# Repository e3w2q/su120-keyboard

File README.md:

# 

Expandable keyboard PCB with up to 120 keys.

## What is the SU120?

The SU120 is an assemblable and expandable keyboard PCB with biscuits, screws and wire.

I use JIS Kana input method, but at that time I couldn't find  split JIS keyboard PCBs.

So I designed the PCB to make the keyboard layout easy to trial and error.

You may make Row-Staggered, Column-Staggerd, Ortholinear, or other layouts keyboard.

SU is Japanese homophones: 州(sandbank) and 鬆(porous).

## Why open source?

Anyone interested in keyboard could try the keyboard layout more easily.

## Link

[Hardware data (PCB)](/pcb/)

[Plate data (PCB)](/plate-pcb/)

[PCB Order Guide](https://github.com/e3w2q/su120-keyboard-doc/blob/master/common/pcb_order_guide.md) / [PCBの入手方法](https://github.com/e3w2q/su120-keyboard-doc/blob/master/common/pcb_order_guide_jp.md)

[Firmware](https://github.com/e3w2q/qmk_firmware/tree/e3w2q/keyboards/e3w2q/su120)

[Remap/VIA Firmware Hex File](/firmware/)

[How to create a custom layout](https://github.com/e3w2q/su120-keyboard-doc/blob/master/custom-layout/readme.md) / [自由なレイアウトを作成するには](https://github.com/e3w2q/su120-keyboard-doc/blob/master/custom-layout/readme_jp.md)

## Example

### 15 Key (+2 Knob) Keypad

[ビルドガイド](https://github.com/e3w2q/su120-keyboard-doc/blob/master/sasami17/readme_jp.md)

### 30 Key Ortholinear Keyboard

[ビルドガイド](https://github.com/e3w2q/su120-keyboard-doc/blob/master/sasami30/readme_jp.md)

### 120 Key Split Ortholinear Keyboard 

[ビルドガイド](https://github.com/e3w2q/su120-keyboard-doc/blob/master/momo120/readme_jp.md)

### 40% Row-Staggered Keyboard

[Photos / ギャラリー](https://github.com/e3w2q/su120-keyboard-doc/blob/master/negima43/readme.md)

### 5% Keyboard

[Photos / ギャラリー](https://github.com/e3w2q/su120-keyboard-doc/blob/master/negima5/readme.md)

### Badge and Clip

[ビルドガイド](https://github.com/e3w2q/su120-keyboard-doc/blob/master/badge_and_clip/readme_jp.md)

### 55% Split Ortholinear Keyboard by [ryuichio](https://twitter.com/ryuichio1)

### [ELEPHANT42](https://twitter.com/hashtag/elephant42?src=hash) Prototype by [🐰](https://twitter.com/illness072)

### Pigeon44 by [🐰](https://twitter.com/illness072)

### 18 Key 2 Knob Low-profile Keypad by [🐰](https://twitter.com/illness072)

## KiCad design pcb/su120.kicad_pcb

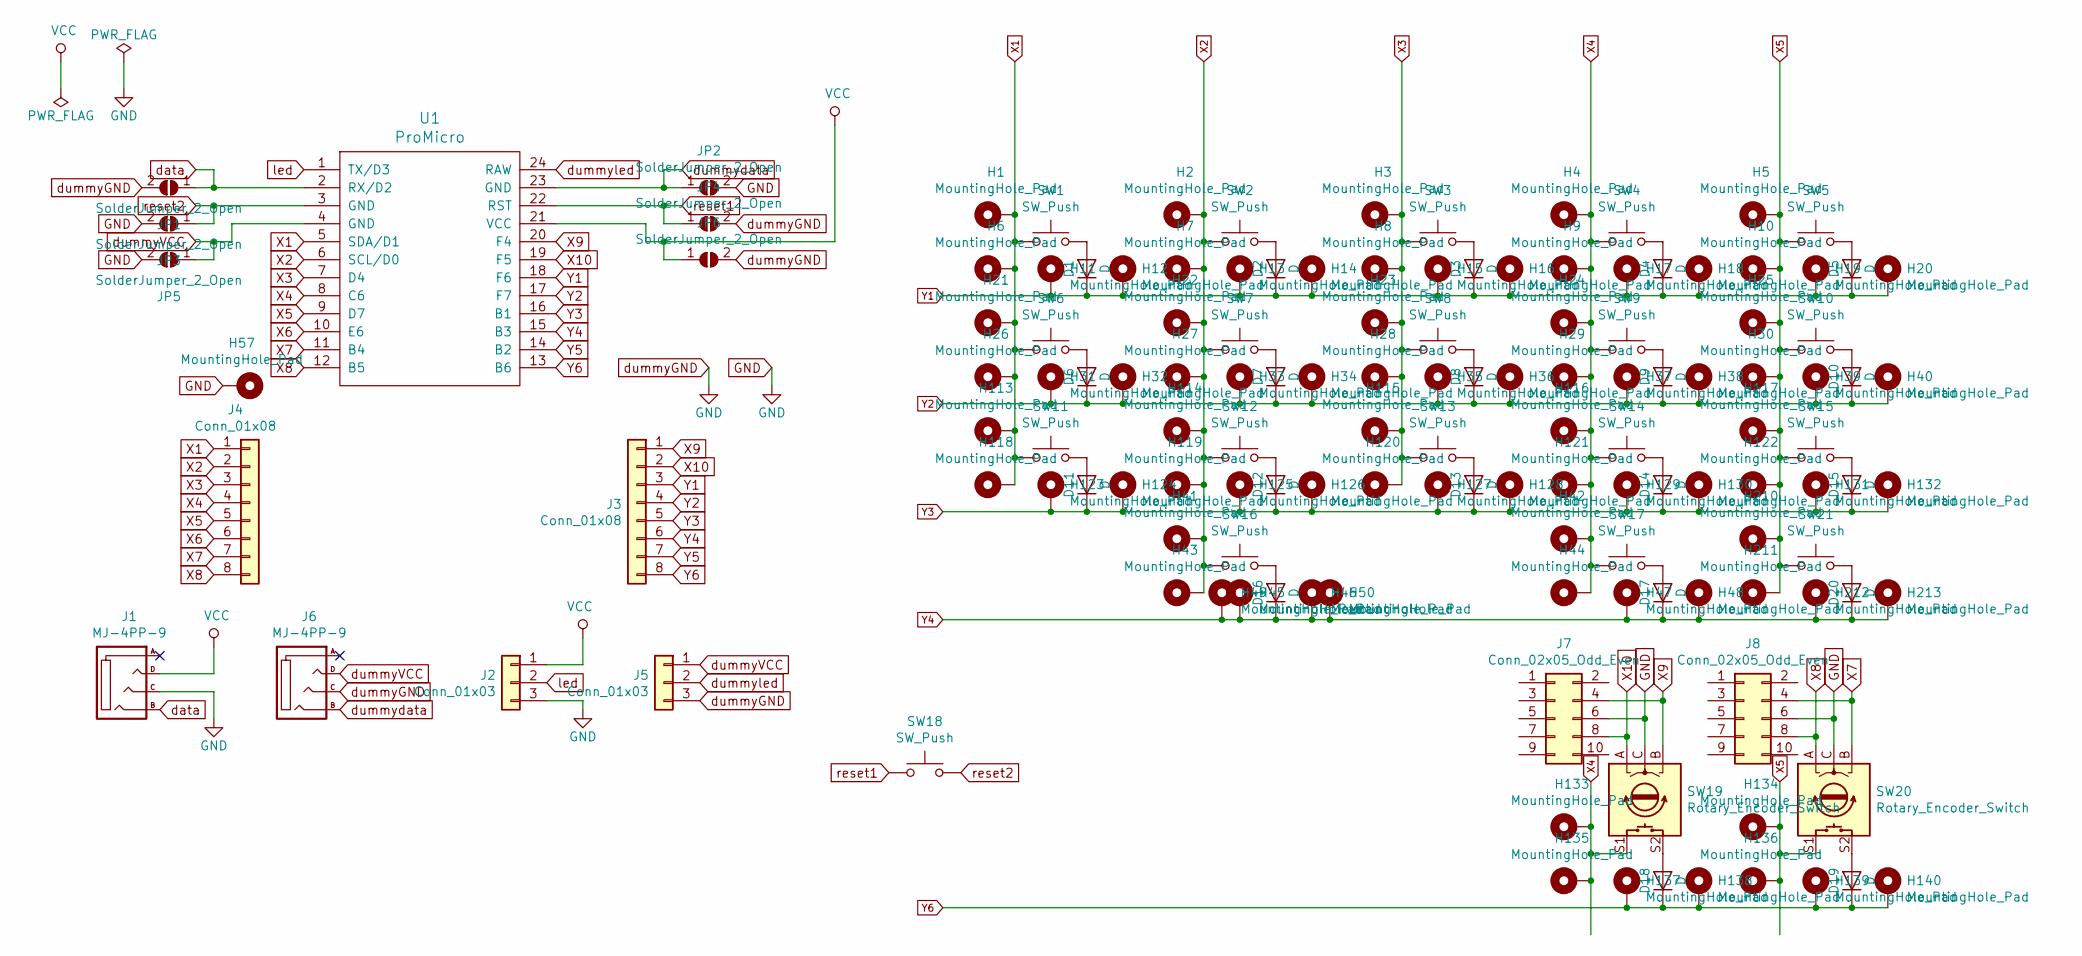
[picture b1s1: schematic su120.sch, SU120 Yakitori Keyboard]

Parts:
D1, D2, D3, D4, D5, D6, D7, D8, D9, D10, D11, D12, D13, D14, D15, D16, D17, D18, D19, D20: D; diode_TH_SMD_rev2
H1, H2, H3, H4, H5, H6, H7, H8, H9, H10, H11, H12, H13, H14, H15, H16, H17, H18, H19, H20, H21, H22, H23, H24, H25, H26, H27, H28, H29, H30, H31, H32, H33, H34, H35, H36, H37, H38, H39, H40, H41, H42, H43, H44, H45, H46, H47, H48, H49, H50, H57, H113, H114, H115, H116, H117, H118, H119, H120, H121, H122, H123, H124, H125, H126, H127, H128, H129, H130, H131, H132, H133, H134, H135, H136, H137, H138, H139, H140, H210, H211, H212, H213: MountingHole_Pad; 1pin_conn
J1, J6: MJ-4PP-9
J2, J5: Conn_01x03; StripLED_rev2
J3, J4: Conn_01x08; PinHeader_1x08_P2.54mm_Vertical_rev2
J7, J8: Conn_02x05_Odd_Even; IDC-Header_2x05_P2.54mm_Vertical
JP1, JP2, JP3, JP4, JP5, JP6: SolderJumper_2_Open; SolderJumper-2_P1.3mm_Open_Pad1.0x1.0mm
SW1, SW2, SW3, SW4, SW5, SW6, SW7, SW8, SW9, SW10, SW11, SW12, SW13, SW14, SW15, SW16, SW17, SW21: SW_Push; CherryMX_MidHeight_Choc_Hotswap_rev5
SW18: SW_Push; ResetSW
SW19, SW20: Rotary_Encoder_Switch; RotaryEncoder_Alps_EC11E-Switch_Vertical_H20mm_rev2
U1: ProMicro; ArduinoProMicro-ZigZag_rev5

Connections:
GND: H57.1, J1.C, J2.3, J5.3, J6.C, J7.6, J8.6, JP1.2 (B), JP2.2 (B), JP3.2 (B), JP4.2 (B), JP5.2 (B), JP6.2 (B), SW19.C, SW20.C
unnamed: D1.2 (A), SW1.2
unnamed: D2.2 (A), SW2.2
unnamed: D3.2 (A), SW3.2
unnamed: D4.2 (A), SW4.2
unnamed: D5.2 (A), SW5.2
unnamed: D6.2 (A), SW6.2
unnamed: D7.2 (A), SW7.2
unnamed: D8.2 (A), SW8.2
unnamed: D9.2 (A), SW9.2
unnamed: D10.2 (A), SW10.2
unnamed: D11.2 (A), SW11.2
unnamed: D12.2 (A), SW12.2
unnamed: D13.2 (A), SW13.2
unnamed: D14.2 (A), SW14.2
unnamed: D15.2 (A), SW15.2
unnamed: D16.2 (A), SW16.2
unnamed: D17.2 (A), SW17.2
unnamed: D18.2 (A), SW19.S2
unnamed: D19.2 (A), SW20.S2
unnamed: D20.2 (A), SW21.2
VCC: J1.D, J2.1, JP6.1 (A), U1.21 (VCC)
X1: H1.1, H6.1, H21.1, H26.1, H113.1, H118.1, J4.1, SW1.1, SW6.1, SW11.1, U1.5 (SDA/D1)
X2: H2.1, H7.1, H22.1, H27.1, H41.1, H43.1, H114.1, H119.1, J4.2, SW2.1, SW7.1, SW12.1, SW16.1, U1.6 (SCL/D0)
X3: H3.1, H8.1, H23.1, H28.1, H115.1, H120.1, J4.3, SW3.1, SW8.1, SW13.1, U1.7 (D4)
X4: H4.1, H9.1, H24.1, H29.1, H42.1, H44.1, H116.1, H121.1, H133.1, H135.1, J4.4, SW4.1, SW9.1, SW14.1, SW17.1, SW19.S1, U1.8 (C6)
X5: H5.1, H10.1, H25.1, H30.1, H117.1, H122.1, H134.1, H136.1, H210.1, H211.1, J4.5, SW5.1, SW10.1, SW15.1, SW20.S1, SW21.1, U1.9 (D7)
X6: J4.6, U1.10 (E6)
X7: J4.7, J8.4, SW20.B, U1.11 (B4)
X8: J4.8, J8.8, SW20.A, U1.12 (B5)
X9: J3.1, J7.4, SW19.B, U1.20 (F4)
X10: J3.2, J7.8, SW19.A, U1.19 (F5)
Y1: D1.1 (K), D2.1 (K), D3.1 (K), D4.1 (K), D5.1 (K), H11.1, H12.1, H13.1, H14.1, H15.1, H16.1, H17.1, H18.1, H19.1, H20.1, J3.3, U1.18 (F6)
Y2: D6.1 (K), D7.1 (K), D8.1 (K), D9.1 (K), D10.1 (K), H31.1, H32.1, H33.1, H34.1, H35.1, H36.1, H37.1, H38.1, H39.1, H40.1, J3.4, U1.17 (F7)
Y3: D11.1 (K), D12.1 (K), D13.1 (K), D14.1 (K), D15.1 (K), H123.1, H124.1, H125.1, H126.1, H127.1, H128.1, H129.1, H130.1, H131.1, H132.1, J3.5, U1.16 (B1)
Y4: D16.1 (K), D17.1 (K), D20.1 (K), H45.1, H46.1, H47.1, H48.1, H49.1, H50.1, H212.1, H213.1, J3.6, U1.15 (B3)
Y5: J3.7, U1.14 (B2)
Y6: D18.1 (K), D19.1 (K), H137.1, H138.1, H139.1, H140.1, J3.8, U1.13 (B6)
data: J1.B, JP1.1 (A), U1.2 (RX/D2)
dummyVCC: J5.1, J6.D, JP5.1 (A), U1.4 (GND)
dummydata: J6.B, JP2.1 (A), U1.23 (GND)
dummyled: J5.2, U1.24 (RAW)
led: J2.2, U1.1 (TX/D3)
reset1: JP4.1 (A), SW18.1, U1.22 (RST)
reset2: JP3.1 (A), SW18.2, U1.3 (GND)

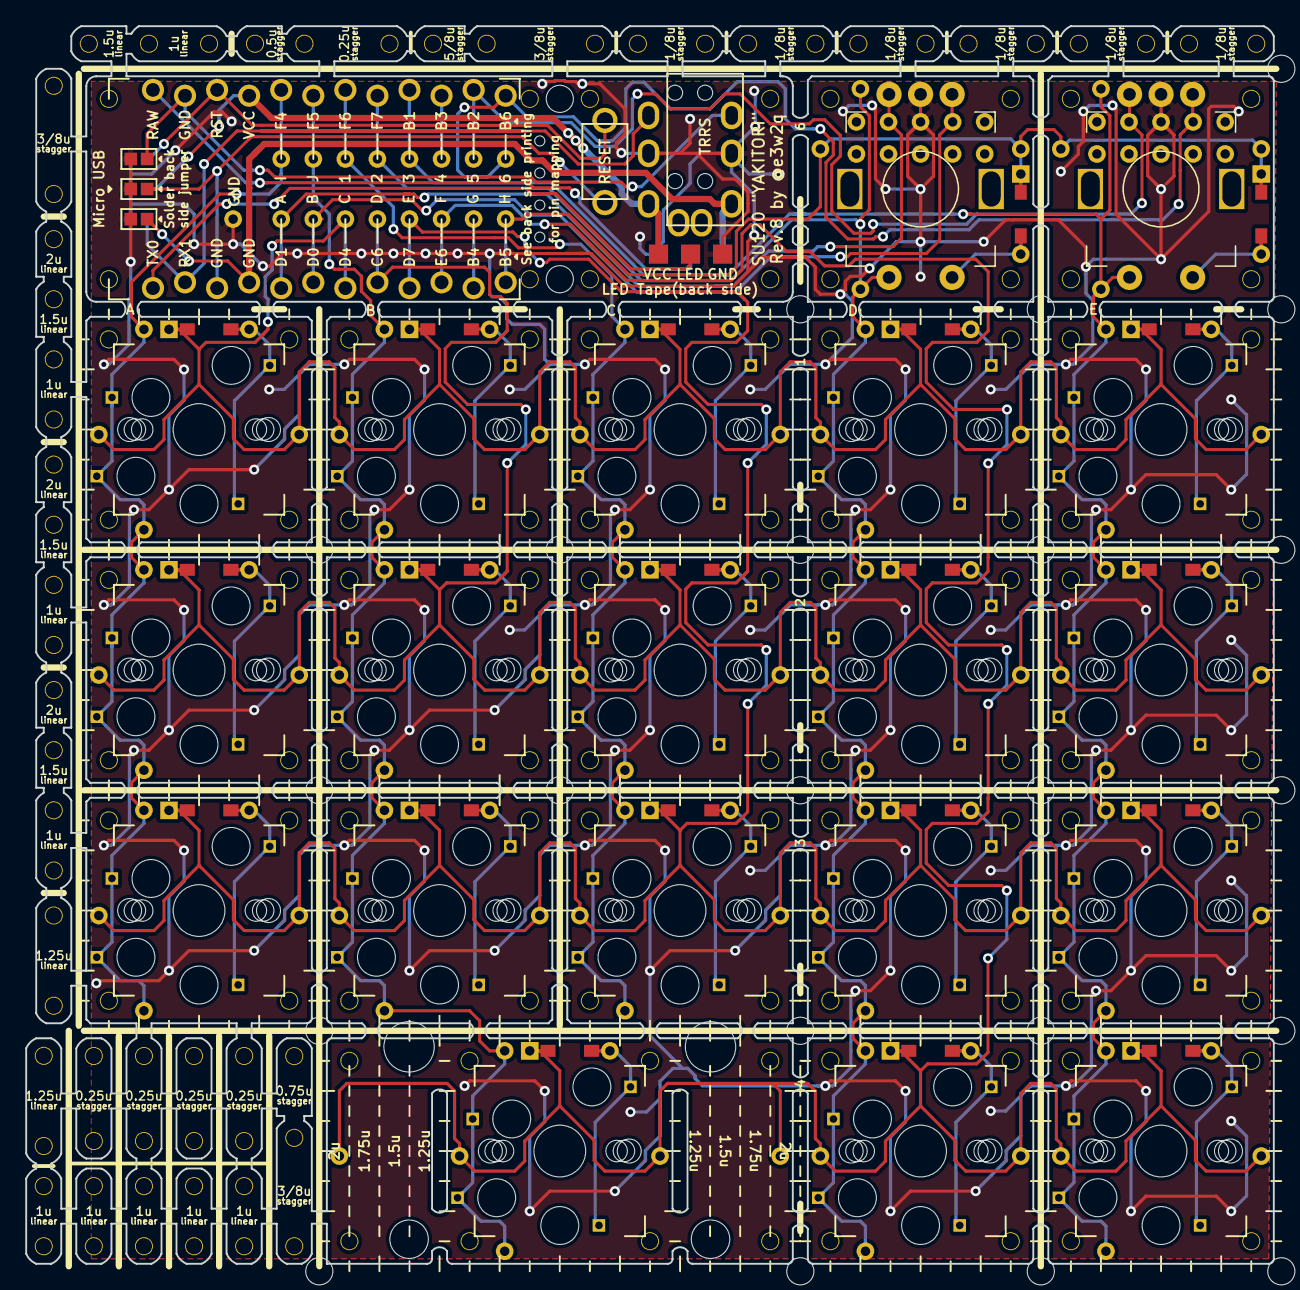
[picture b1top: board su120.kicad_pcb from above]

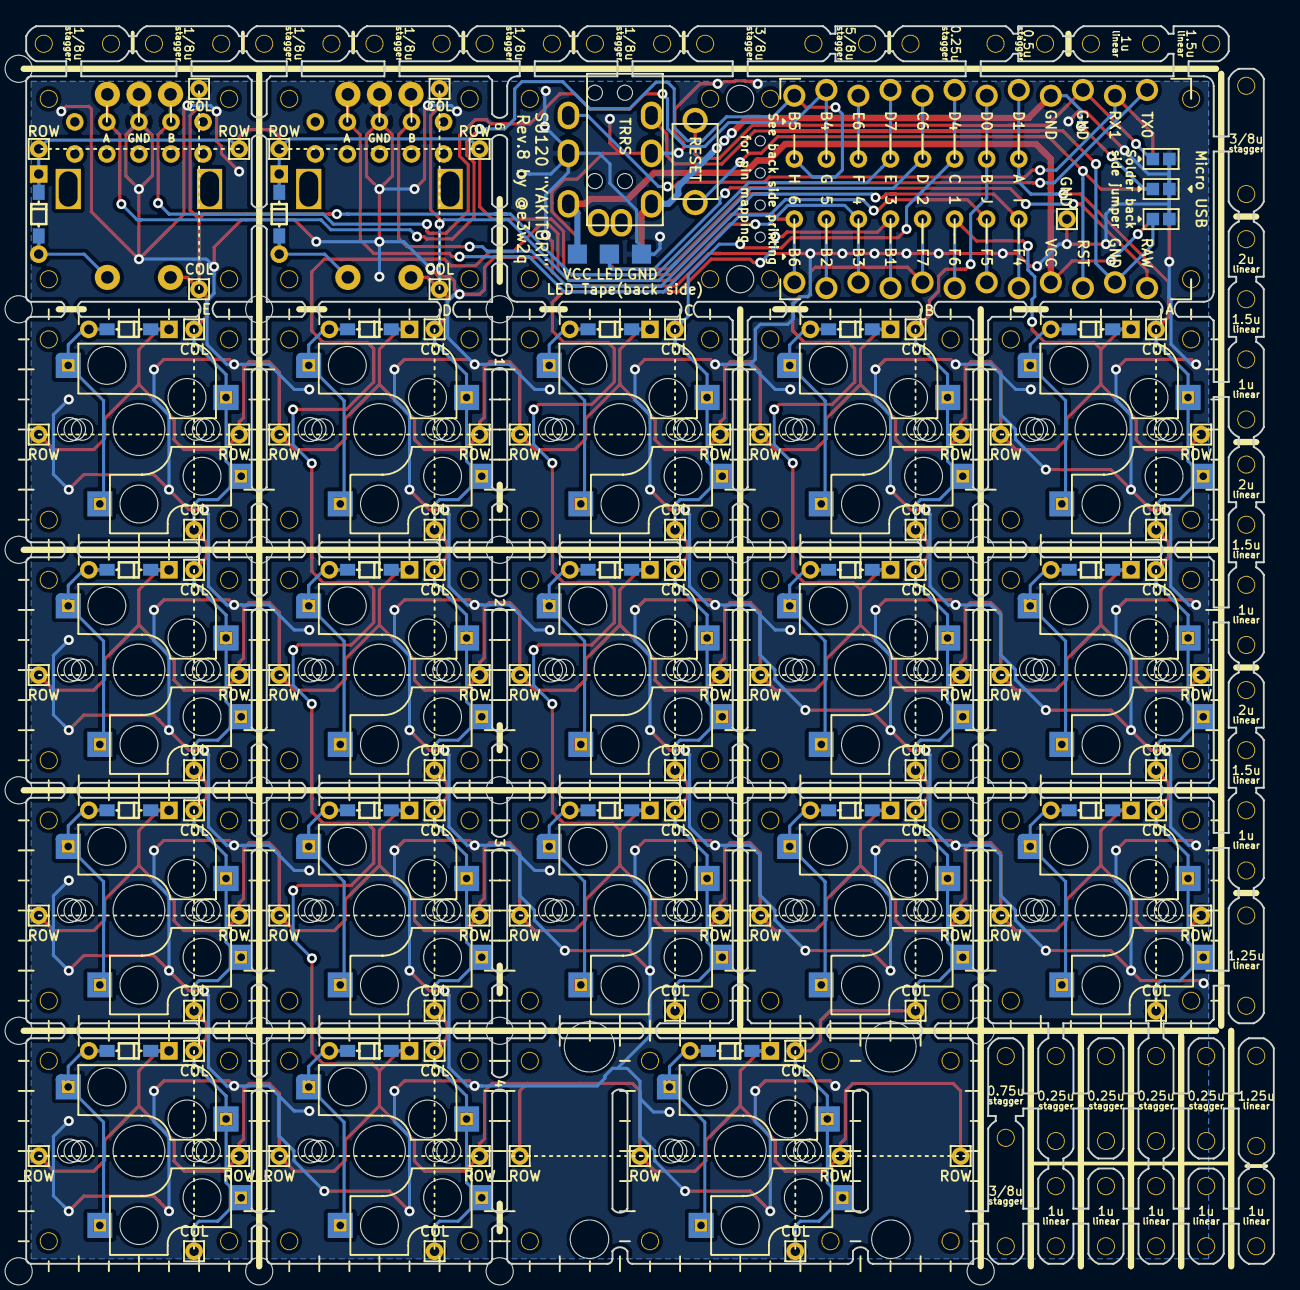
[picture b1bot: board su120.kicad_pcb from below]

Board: 2 copper layers, 98.8 x 98.0 mm, 139 parts (6 on the bottom side), 45 nets.

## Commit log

2019-05-29 temporary
2019-06-02 revise
2019-06-04 add tool guide
2019-06-04 Add sample
2019-06-09 update text
2019-06-20 Rev.3
2019-07-04 Rev.4
2019-07-05 footprint add
2019-07-06 fix PCB
2019-07-22 rev5
2019-09-02 Rev6
2019-09-16 Rotary Encoder's pin exchanged
2019-09-17 add plate PCB
2019-10-02 Rev.7
2019-10-02 Rev.2
2019-11-24 update and add plate120-pcb
2020-01-06 Rev.8
2020-01-14 adjust silk and hole size
2020-05-06 Add acrylic case data
2021-03-12 Add Remap Firmware Hex File
2022-02-09 40% Column-Staggered → 40% Row-Staggered
    Negima43 is row-staggered, not columnar-staggered
2023-01-30 Fixed malformed outline errors
2023-01-30 Minor trace adjustment to fix edge clearance violations
2023-01-30 Regenerated Fills
2023-01-30 Rebuilt gerbers

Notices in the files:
README.md:
License: MIT
